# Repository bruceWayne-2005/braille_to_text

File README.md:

# Braille to Text Converter - PCB Schematic & Layout

## Project Overview

This project aims to create a **Braille to Text Converter**, a device that converts Braille input into digital text. This repository includes the **PCB schematic** and **layout** for the converter.

## Getting Started

1. Clone the repository:
   ```bash
   git clone https://github.com/yourusername/braille-to-text-pcb.git

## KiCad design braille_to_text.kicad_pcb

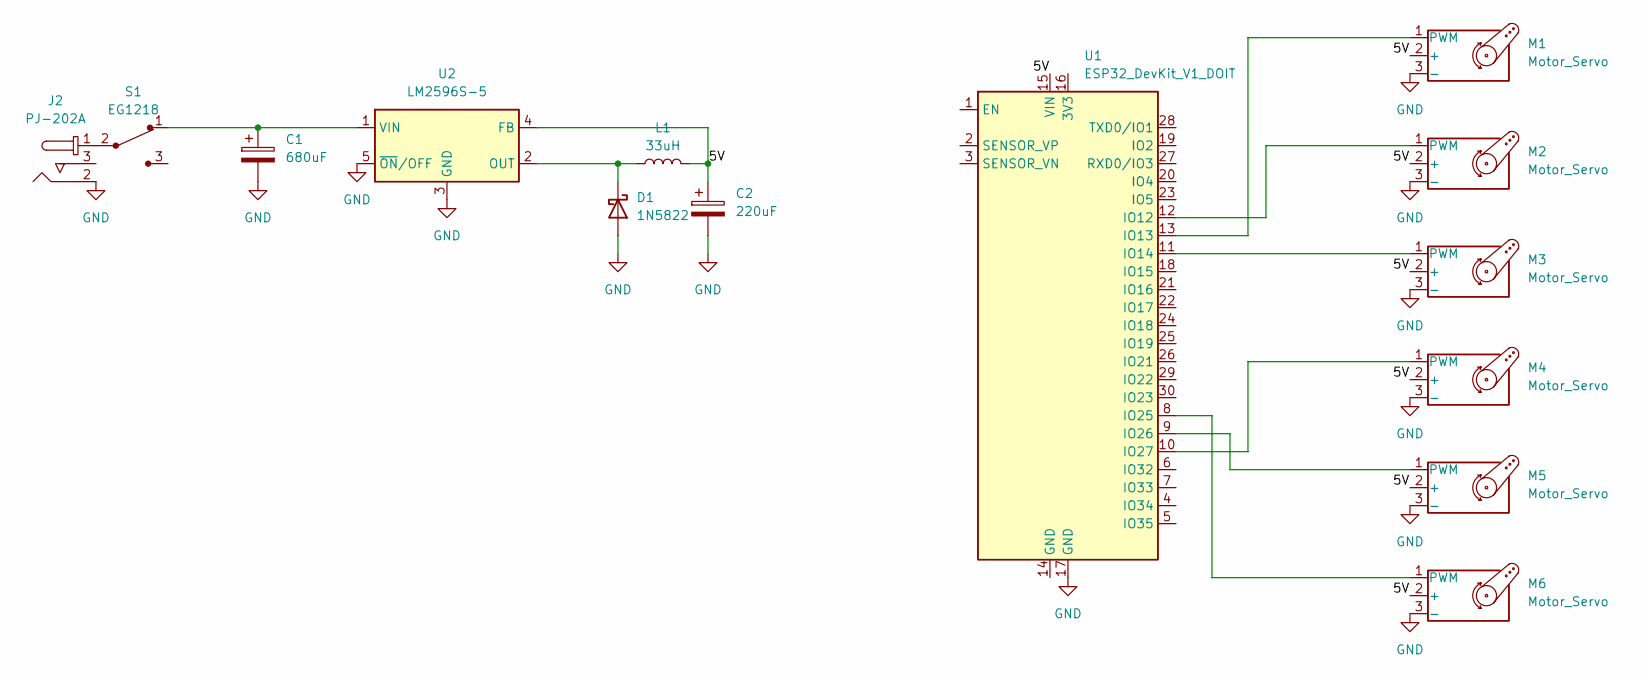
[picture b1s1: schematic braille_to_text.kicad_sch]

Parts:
C1: 680uF; CP_Radial_D16.0mm_P7.50mm
C2: 220uF; CP_Radial_D6.3mm_P2.50mm
D1: 1N5822; D_DO-201AD_P15.24mm_Horizontal
J2: PJ-202A; Barrel_Jack_5.5mmODx2.1mmID_PJ-202A; MPN PJ-202A; Digi-Key_PN CP-202A-ND
L1: 33uH; L_Toroid_Vertical_L13.0mm_W6.5mm_P5.60mm
M1, M2, M3, M4, M5, M6: Motor_Servo; PinHeader_1x03_P2.54mm_Vertical
S1: EG1218; Switch_Slide_11.6x4mm_EG1218; MPN EG1218; Digi-Key_PN EG1903-ND
U1: ESP32_DevKit_V1_DOIT; esp32_devkit_v1_doit
U2: LM2596S-5; TO-263-5_TabPin3

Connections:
/5V: C2.1, L1.2, M1.2 (+), M2.2 (+), M3.2 (+), M4.2 (+), M5.2 (+), M6.2 (+), U1.15 (VIN), U2.4 (FB)
GND: C1.2, C2.2, D1.2 (A), J2.2, M1.3 (-), M2.3 (-), M3.3 (-), M4.3 (-), M5.3 (-), M6.3 (-), U1.17 (GND), U2.3 (GND), U2.5 (~ON/OFF)
unnamed: D1.1 (K), L1.1, U2.2 (OUT)
unnamed: J2.1, S1.2
unnamed: M1.1 (PWM), U1.13 (IO13)
unnamed: M2.1 (PWM), U1.12 (IO12)
unnamed: M3.1 (PWM), U1.11 (IO14)
unnamed: M4.1 (PWM), U1.10 (IO27)
unnamed: M5.1 (PWM), U1.9 (IO26)
unnamed: M6.1 (PWM), U1.8 (IO25)
unnamed: C1.1, S1.1, U2.1 (VIN)

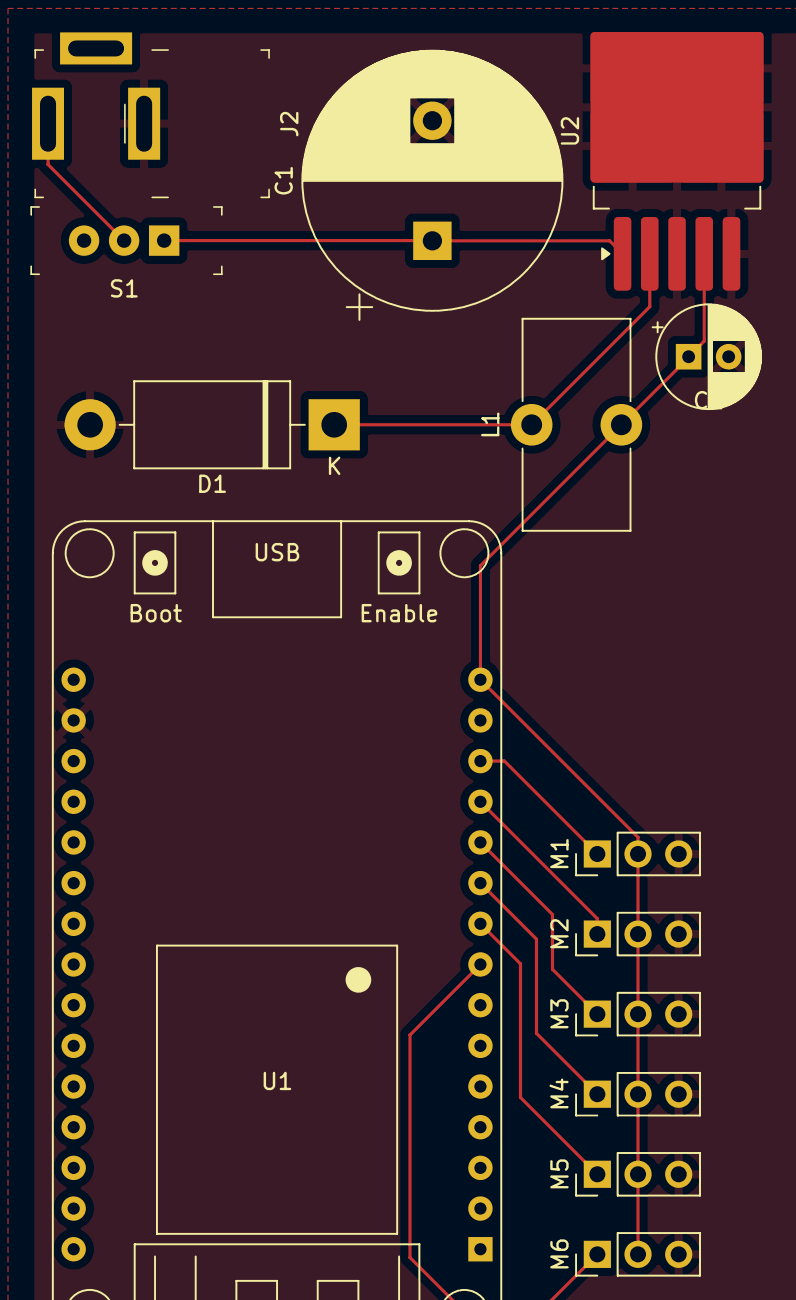
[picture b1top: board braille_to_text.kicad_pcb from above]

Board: 2 copper layers, 14 parts (0 on the bottom side), 11 nets.

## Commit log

2025-03-31 added files
